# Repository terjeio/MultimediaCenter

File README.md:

# Multimedia center with DAB/FM radio

Features:

High quality (IMO) pre-amp board with I2C control of inputs and VCA based volume control.

5 line inputs, one may be fitted with an internal RIAA-preamp (phono, for moving magnet cartridges).
2 line outputs with old-style tape copy function and post listening possible.

Power amplifier on/off switching via inbuilt relay river.

KeyStone DAB/FM-module may be fitted.

Custom Raspberry PI power switch with PC-style startup/shutdown, may be controlled over I2C or from a front panel button.
Has "breakout" socket for internal USB HDD.

IR Remote Control - RC5 protocol: for input selection, volume control and UI controller navigation.

Main controller built around a Texas Instruments Tiva C MPU, custom UI library with support for KeyStone radio-module.

Raspberry PI for media playback (via Kodi), in my configuration audio is fed via HDMI to a TV and then to a DAC mounted inside the pre-amp cabinet.

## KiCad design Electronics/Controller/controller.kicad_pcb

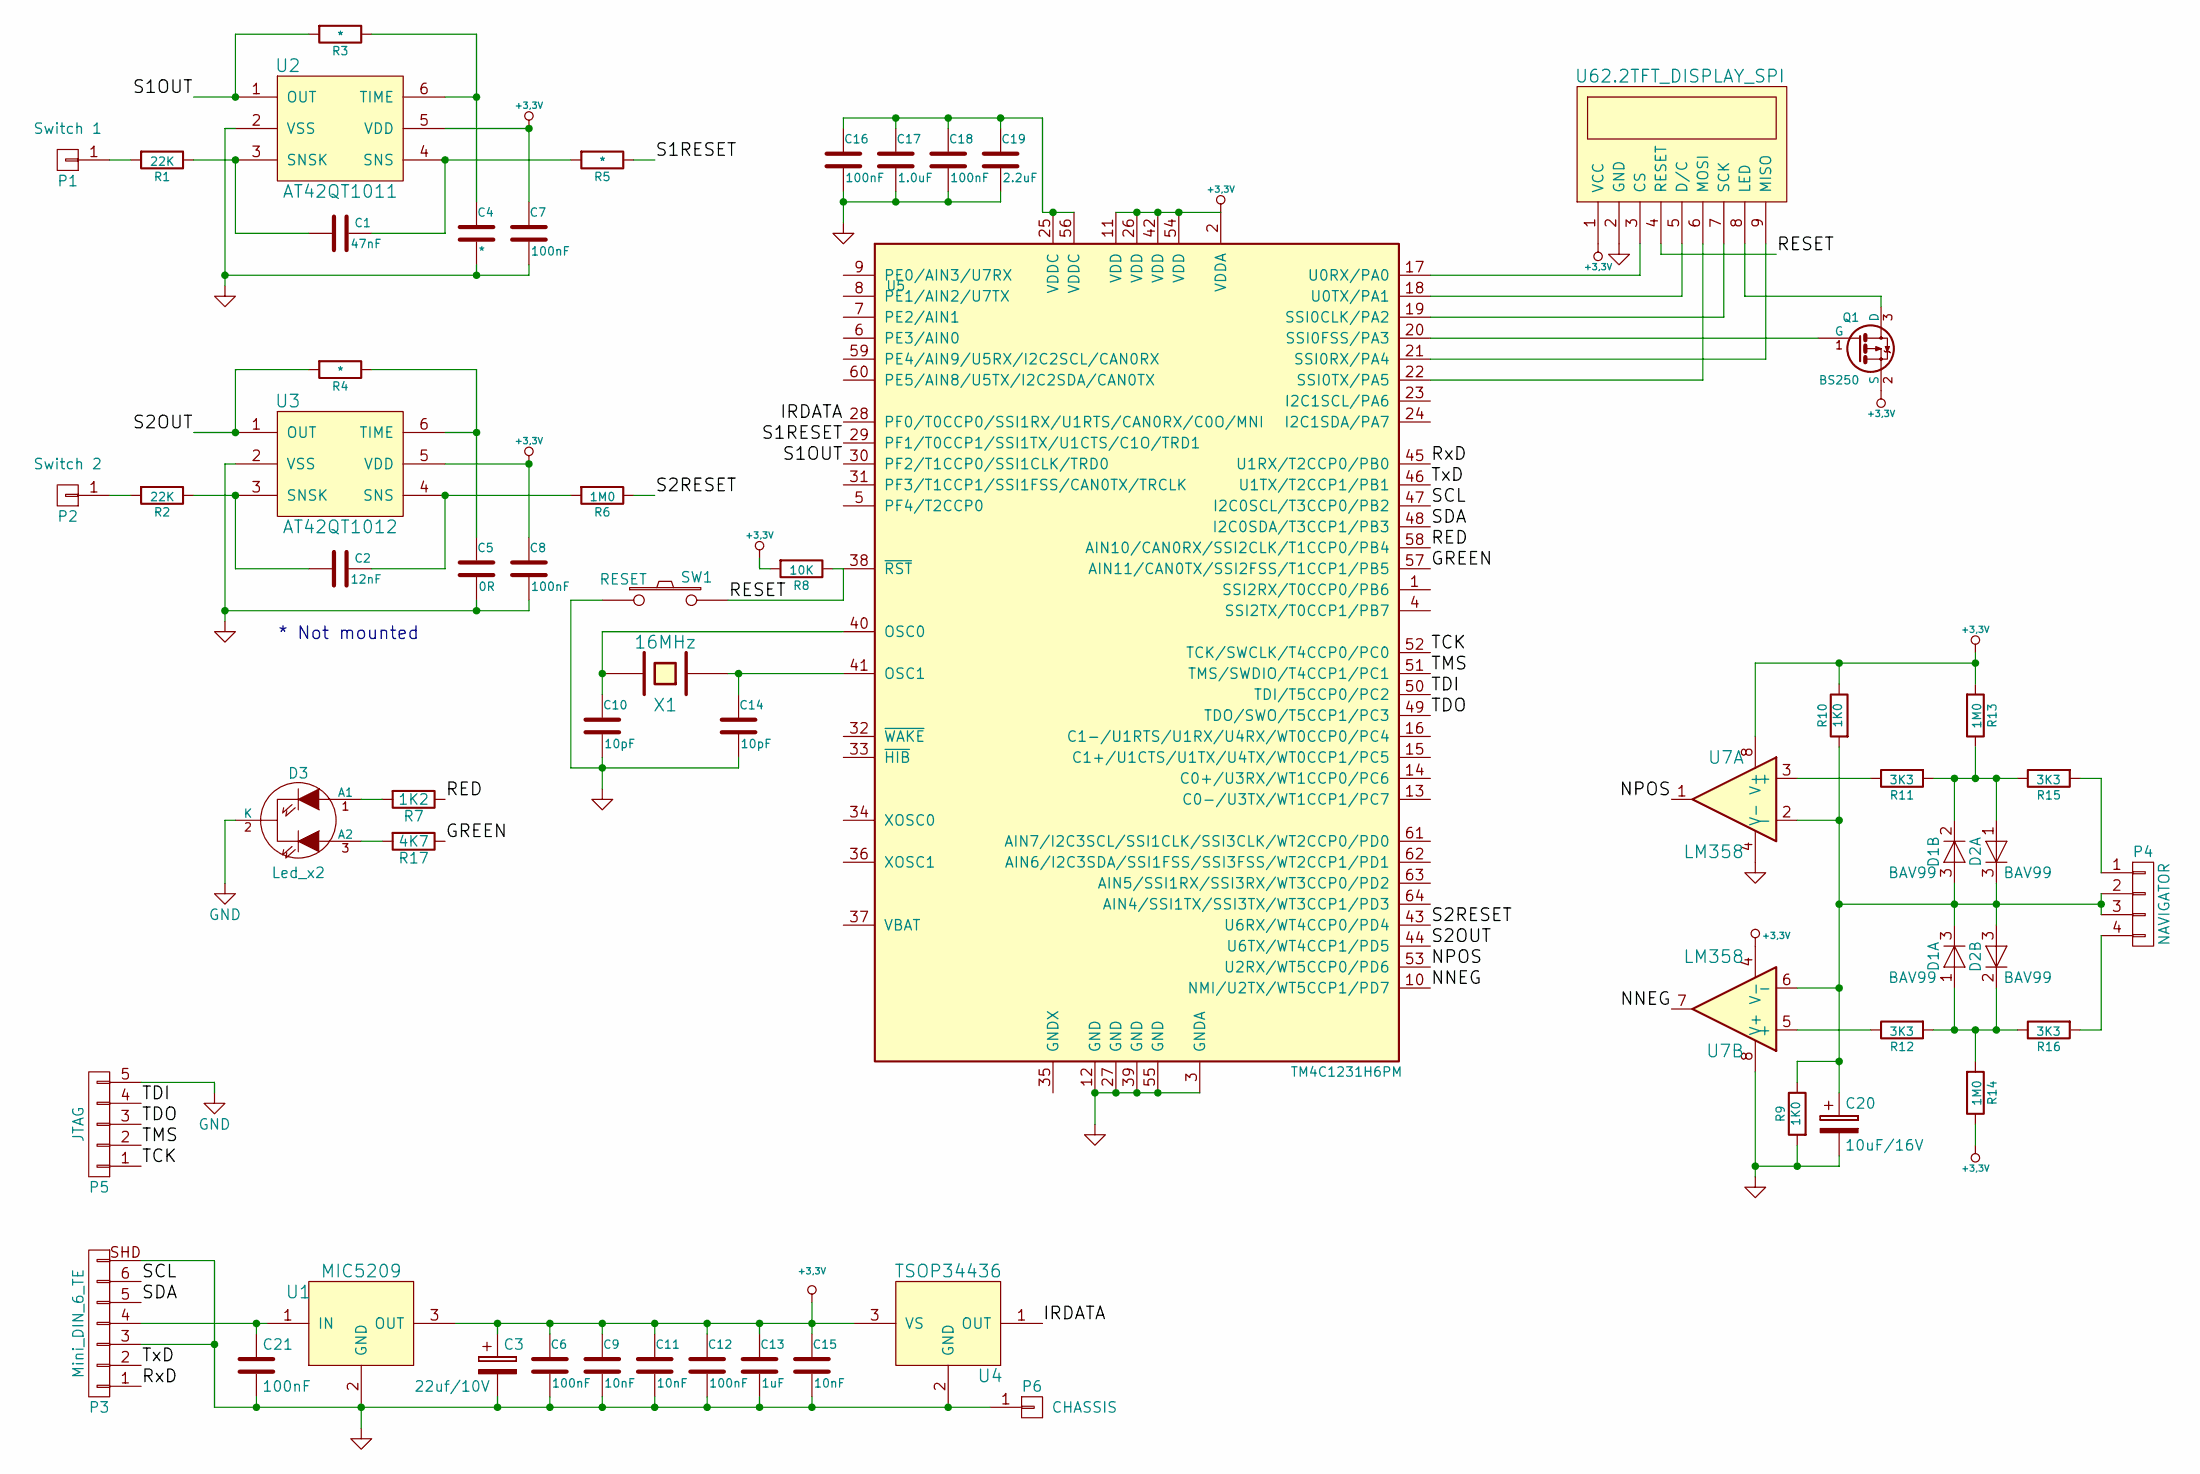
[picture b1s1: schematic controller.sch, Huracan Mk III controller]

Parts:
C1: 47nF; C_0805
C2: 12nF; C_0805
C3: 22uf/10V; TantalC_SizeA_EIA-3216_Reflow
C4: *; C_0805
C5: 0R; C_0805
C6, C7, C8, C12, C16, C18, C21: 100nF; C_0805
C9, C11, C15: 10nF; C_0805
C10, C14: 10pF; C_0805
C13: 1uF; C_0805
C17: 1.0uF; C_0805
C19: 2.2uF; C_1206
C20: 10uF/16V; TantalC_SizeA_EIA-3216_Reflow
D1, D2: BAV99; SOT-23
D3: Led_x2; LED-3MM-2
P1: Switch 1; Pin_Header_Straight_1x01
P2: Switch 2; Pin_Header_Straight_1x01
P3: Mini_DIN_6_TE; Mini_DIN_6_TE_Connectivity
P4: NAVIGATOR; Pin_Header_Straight_1x04
P5: JTAG; Pin_Header_Straight_1x05
P6: CHASSIS; Socket_Strip_Straight_1x01
Q1: BS250; SOT-23
R1, R2: 22K; R_1206
R3, R4, R5: *; R_1206
R6, R13, R14: 1M0; R_1206
R7: 1K2; R_1206
R8: 10K; R_1206
R9, R10: 1K0; R_1206
R11, R12, R15, R16: 3K3; R_1206
R17: 4K7; R_1206
SW1: RESET; SWITCH_TAC_H7.3
U1: MIC5209; SOT223
U2: AT42QT1011; SOT23-6
U3: AT42QT1012; SOT23-6
U4: TSOP34436; Pin_Header_Straight_1x03
U5: TM4C1231H6PM; LQFP-64_10x10mm_Pitch0.5mm
U6: 2.2TFT_DISPLAY_SPI; QVGA_2.2
U7: LM358; SO-8
X1: 16MHz; XTAL_ABM7_6x3.5MM

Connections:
/GREEN: R17.1, U5.57 (AIN11/CAN0TX/SSI2FSS/T1CCP1/PB5)
/IRDATA: U4.1 (OUT), U5.28 (PF0/T0CCP0/SSI1RX/U1RTS/CAN0RX/C0O/MNI)
/NNEG: U5.10 (NMI/U2TX/WT5CCP1/PD7), U7.7
/NPOS: U5.53 (U2RX/WT5CCP0/PD6), U7.1
/RED: R7.1, U5.58 (AIN10/CAN0RX/SSI2CLK/T1CCP0/PB4)
/RESET: R8.1, SW1.2, U5.38 (~RST~), U6.4 (RESET)
/RxD: P3.1, U5.45 (U1RX/T2CCP0/PB0)
/S1OUT: R3.2, U2.1 (OUT), U5.30 (PF2/T1CCP0/SSI1CLK/TRD0)
/S1RESET: R5.1, U5.29 (PF1/T0CCP1/SSI1TX/U1CTS/C1O/TRD1)
/S2OUT: R4.2, U3.1 (OUT), U5.44 (U6TX/WT4CCP1/PD5)
/S2RESET: R6.1, U5.43 (U6RX/WT4CCP0/PD4)
/SCL: P3.6, U5.47 (I2C0SCL/T3CCP0/PB2)
/SDA: P3.5, U5.48 (I2C0SDA/T3CCP1/PB3)
/TCK: P5.1, U5.52 (TCK/SWCLK/T4CCP0/PC0)
/TDI: P5.4, U5.50 (TDI/T5CCP0/PC2)
/TDO: P5.3, U5.49 (TDO/SWO/T5CCP1/PC3)
/TMS: P5.2, U5.51 (TMS/SWDIO/T4CCP1/PC1)
/TxD: P3.2, U5.46 (U1TX/T2CCP1/PB1)
unnamed: C1.1, R1.1, U2.3 (SNSK)
unnamed: C1.2, R5.2, U2.4 (SNS)
unnamed: C2.1, R2.1, U3.3 (SNSK)
unnamed: C2.2, R6.2, U3.4 (SNS)
unnamed: C4.1, R3.1, U2.6 (TIME)
unnamed: C5.1, R4.1, U3.6 (TIME)
unnamed: C10.1, U5.40 (OSC0), X1.2
unnamed: C14.1, U5.41 (OSC1), X1.1
unnamed: C16.1, C17.1, C18.1, C19.1, U5.25 (VDDC), U5.56 (VDDC)
unnamed: C20.1, D1.3 (K), D2.3 (K), P4.2, P4.3, R9.1, R10.2, U7.2 (-), U7.6 (-)
unnamed: C21.1, P3.4, U1.1 (IN)
unnamed: D1.1 (A), D2.2 (K), R12.2, R14.2, R16.1
unnamed: D1.2 (K), D2.1 (A), R11.2, R13.1, R15.1
unnamed: D3.1 (A1), R7.2
unnamed: D3.3 (A2), R17.2
unnamed: P1.1, R1.2
unnamed: P2.1, R2.2
unnamed: P4.1, R15.2
unnamed: P4.4, R16.2
unnamed: Q1.1 (G), U5.20 (SSI0FSS/PA3)
unnamed: Q1.3 (D), U6.8 (LED)
unnamed: R11.1, U7.3 (+)
unnamed: R12.1, U7.5 (+)
unnamed: U5.17 (U0RX/PA0), U6.3 (CS)
unnamed: U5.18 (U0TX/PA1), U6.5 (D/C)
unnamed: U5.19 (SSI0CLK/PA2), U6.7 (SCK)
unnamed: U5.21 (SSI0RX/PA4), U6.9 (MISO)
unnamed: U5.22 (SSI0TX/PA5), U6.6 (MOSI)

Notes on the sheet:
* Not mounted

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
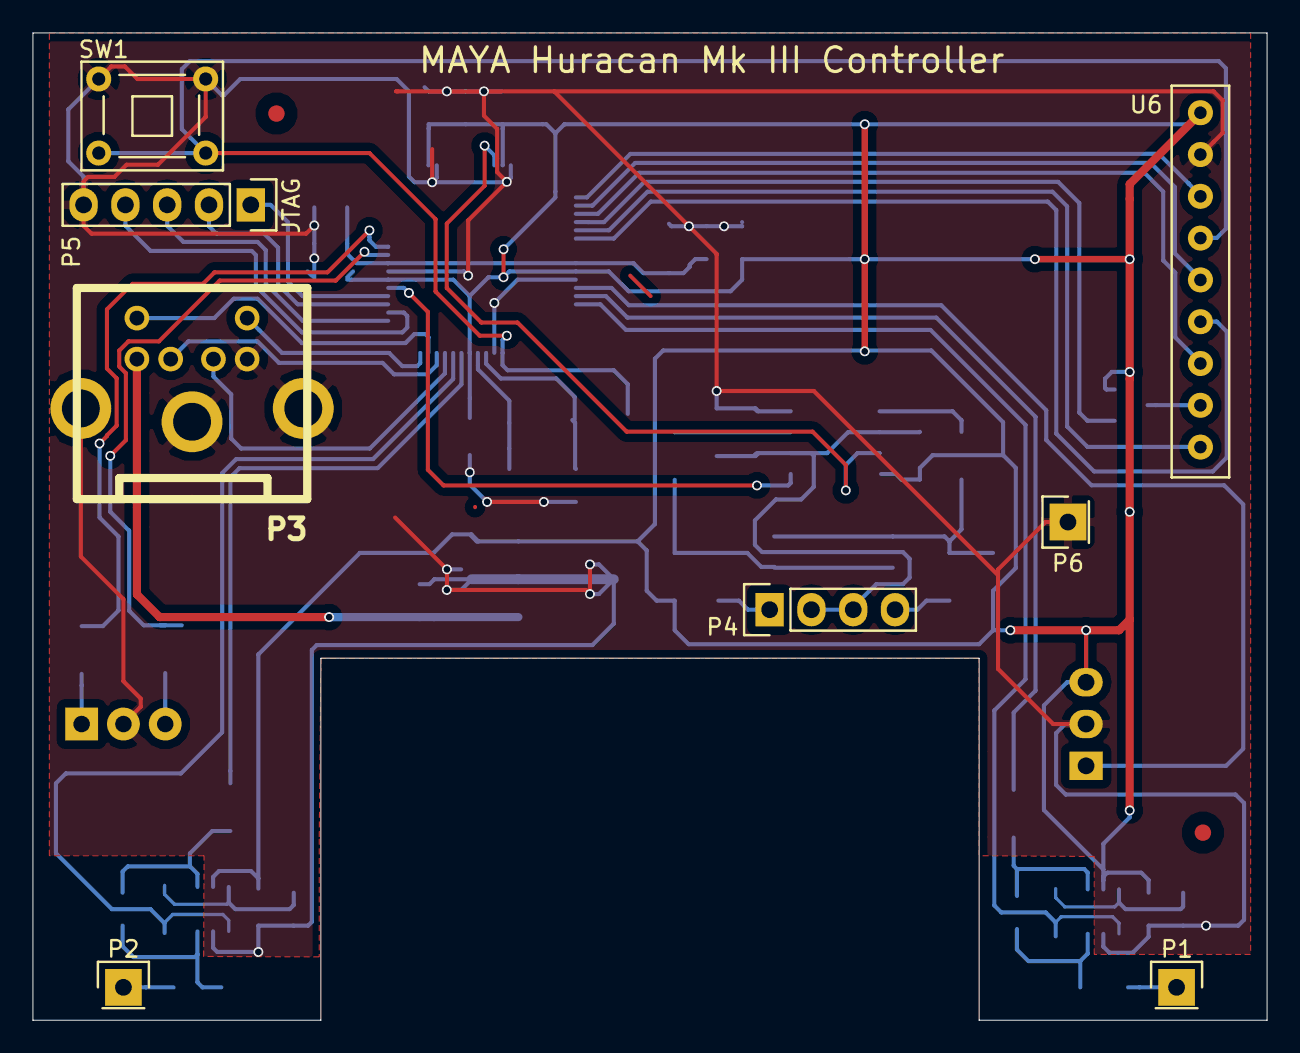
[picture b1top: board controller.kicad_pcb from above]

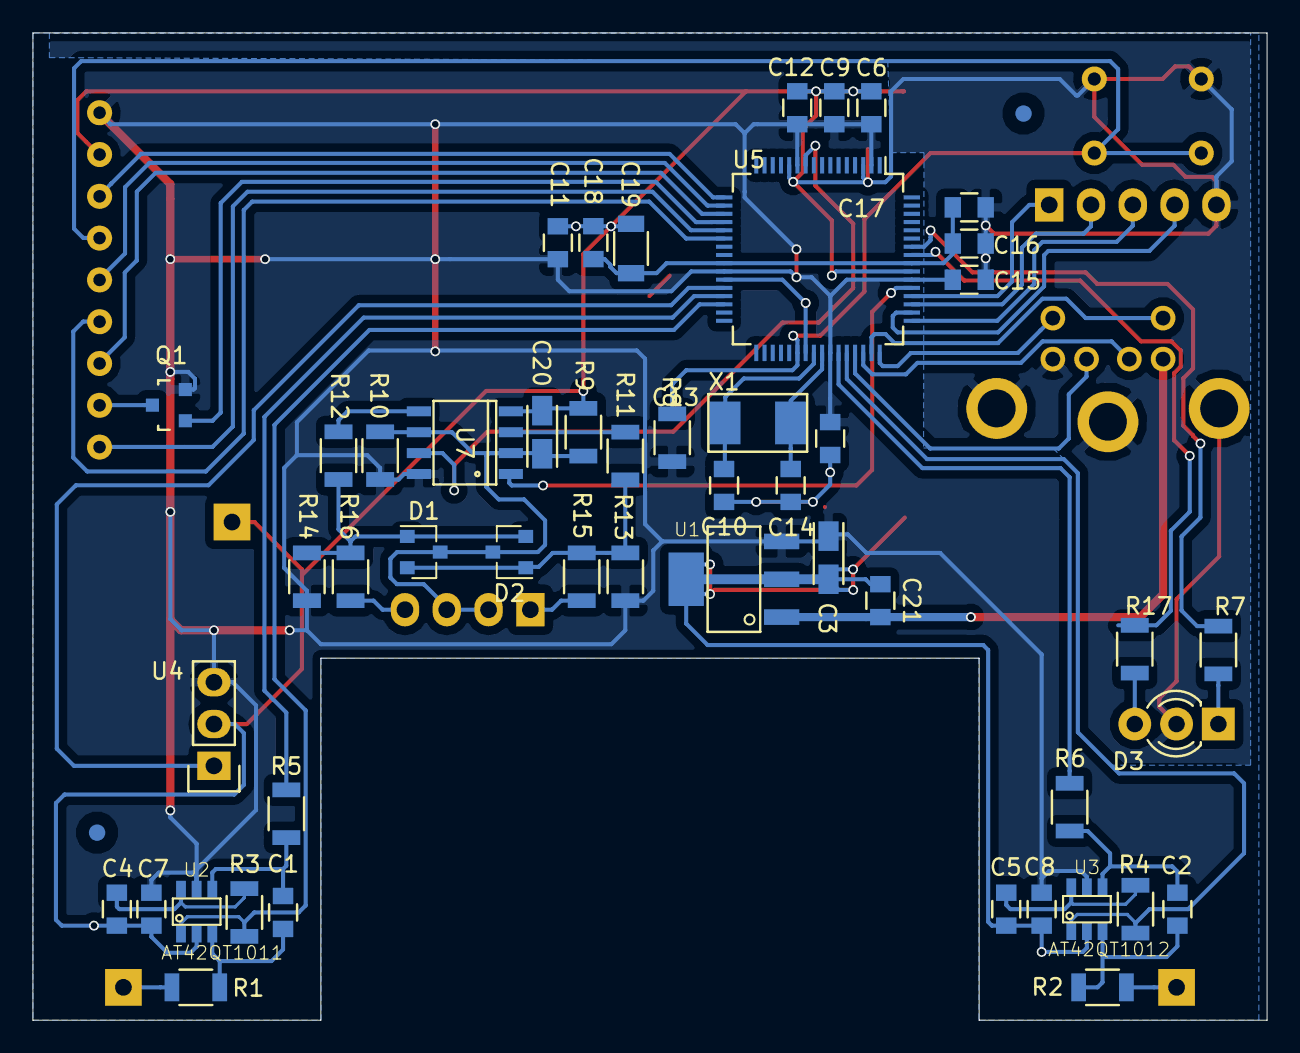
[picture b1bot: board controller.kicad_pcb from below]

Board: 2 copper layers, 75.0 x 60.0 mm, 57 parts (49 on the bottom side), 48 nets.

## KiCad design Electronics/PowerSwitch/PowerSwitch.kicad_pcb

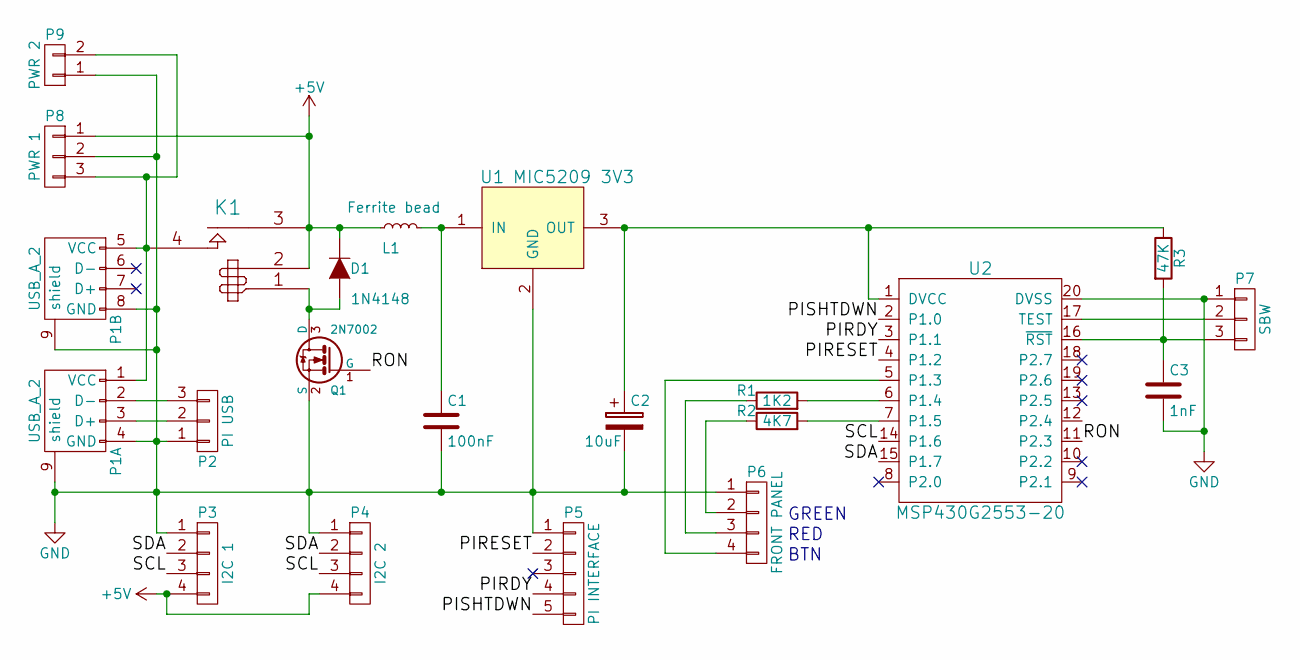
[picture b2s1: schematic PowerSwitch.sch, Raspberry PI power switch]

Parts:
C1: 100nF; C_1206
C2: 10uF; TantalC_SizeA_EIA-3216_Reflow
C3: 1nF; C_1206
D1: 1N4148; SOD-123
K1: RELAY-LD-P; PANASONIC_LD_P_RELAY
L1: Ferrite bead; Resistor_Horizontal_RM10mm
P1: USB_A_2
P2: PI USB; Pin_Header_Straight_1x03
P3: I2C 1; Pin_Header_Straight_1x04
P4: I2C 2; Pin_Header_Straight_1x04
P5: PI INTERFACE; Pin_Header_Straight_1x05
P6: FRONT PANEL; Pin_Header_Straight_1x04
P7: SBW; Pin_Header_Straight_1x03
P8: PWR 1; CONN_PWR_3P
P9: PWR 2; Pin_Header_Straight_1x02
Q1: 2N7002; SOT-23
R1: 1K2; R_1206
R2: 4K7; R_1206
R3: 47K; R_1206
U1: MIC5209 3V3; AB2_SOT223
U2: MSP430G2553-20; TSSOP20

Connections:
+5V: D1.1 (K), K1.2, K1.3, L1.1, P3.4, P4.4, P8.1
/PIRDY: P5.4, U2.3 (P1.1)
/PIRESET: P5.2, U2.4 (P1.2)
/PISHTDWN: P5.5, U2.2 (P1.0)
/RON: Q1.1 (G), U2.11 (P2.3)
/SCL: P3.3, P4.3, U2.14 (P1.6)
/SDA: P3.2, P4.2, U2.15 (P1.7)
GND: C1.2, C2.2, C3.2, P1.4 (GND), P1.8 (GND), P1.9 (shield), P2.1, P3.1, P4.1, P5.1, P6.1, P7.1, P8.2, P9.1, Q1.2 (S), U1.2 (GND), U2.20 (DVSS)
unnamed: C1.1, L1.2, U1.1 (IN)
unnamed: C2.1, R3.1, U1.3 (OUT), U2.1 (DVCC)
unnamed: C3.1, P7.3, R3.2, U2.16 (~RST~)
unnamed: D1.2 (A), K1.1, Q1.3 (D)
unnamed: K1.4, P1.1 (VCC), P1.5 (VCC), P8.3, P9.2
unnamed: P1.2 (D-), P2.3
unnamed: P1.3 (D+), P2.2
unnamed: P6.2, R2.1
unnamed: P6.3, R1.1
unnamed: P6.4, U2.5 (P1.3)
unnamed: P7.2, U2.17 (TEST)
unnamed: R1.2, U2.6 (P1.4)
unnamed: R2.2, U2.7 (P1.5)

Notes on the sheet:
RED
GREEN
BTN

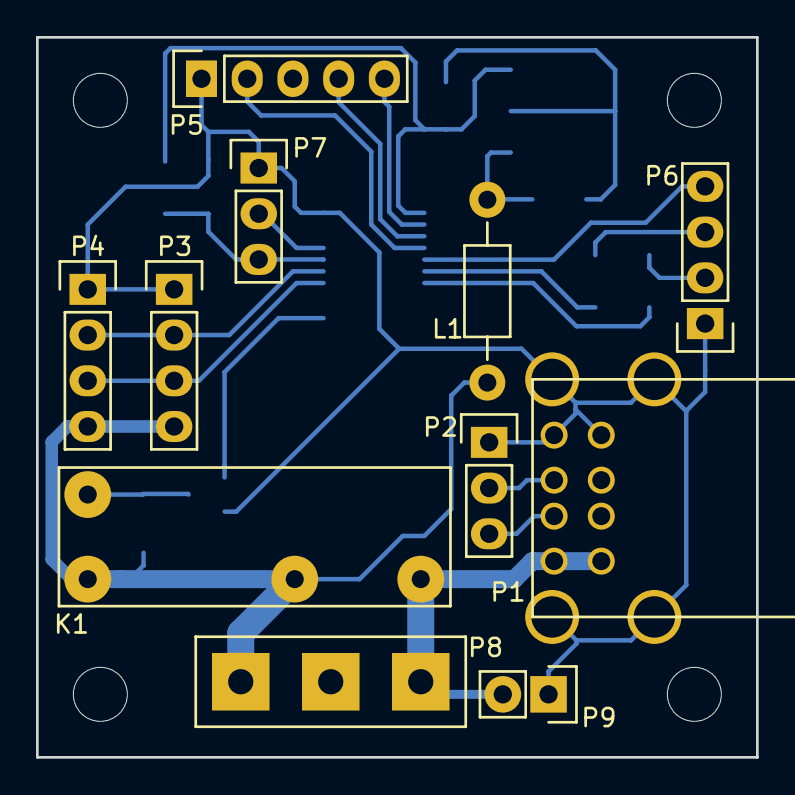
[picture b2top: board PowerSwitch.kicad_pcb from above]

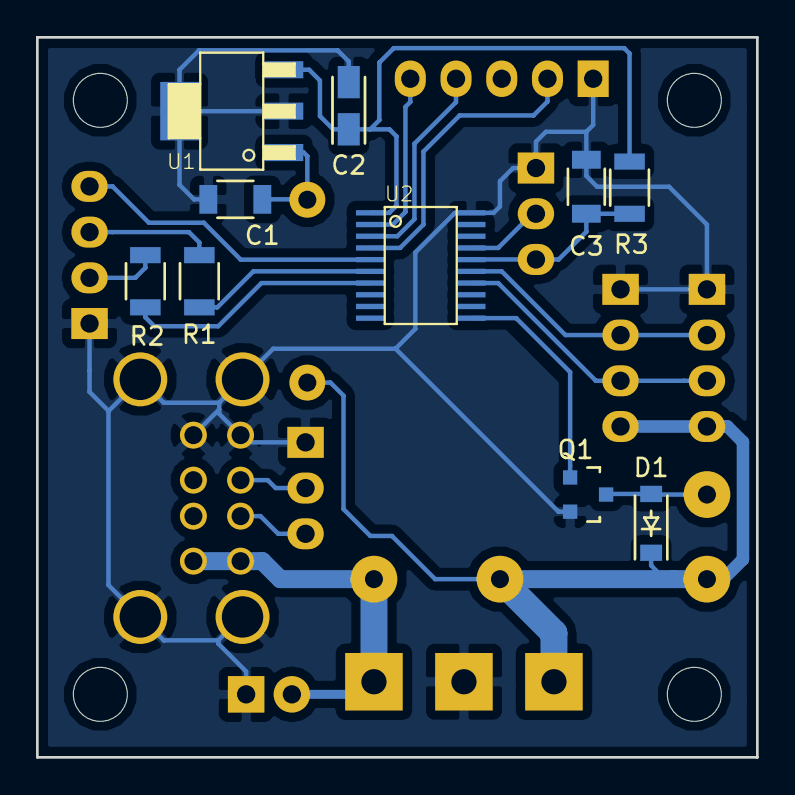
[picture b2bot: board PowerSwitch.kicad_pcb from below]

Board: 2 copper layers, 40.0 x 40.0 mm, 21 parts (10 on the bottom side), 21 nets.

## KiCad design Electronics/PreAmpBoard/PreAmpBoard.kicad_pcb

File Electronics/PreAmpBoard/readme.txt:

MAYA Huracan PreAmp MK III Rev. A by

Terje Io
Io Engineering

Licensed under CERN OHL v.1.2 or later except the RIAA-circuitry which I believe is public domain.

The RIAA-circuitry was published by now defunct danish magazine High Fidelity way back in the 1980's.
I no longer have a copy of the issue(s) related to the design so I am not sure about any related copyright
but it surely is available for non-commercial use.

NOTE: Rev A has not yet been been verified as a working design.

Firmware will be released as a separate package under a different license after the design is verified.

A limited number of PCBs might or might not be made available for purchase at cost.

Files are in KiCad format.

2017-09-18

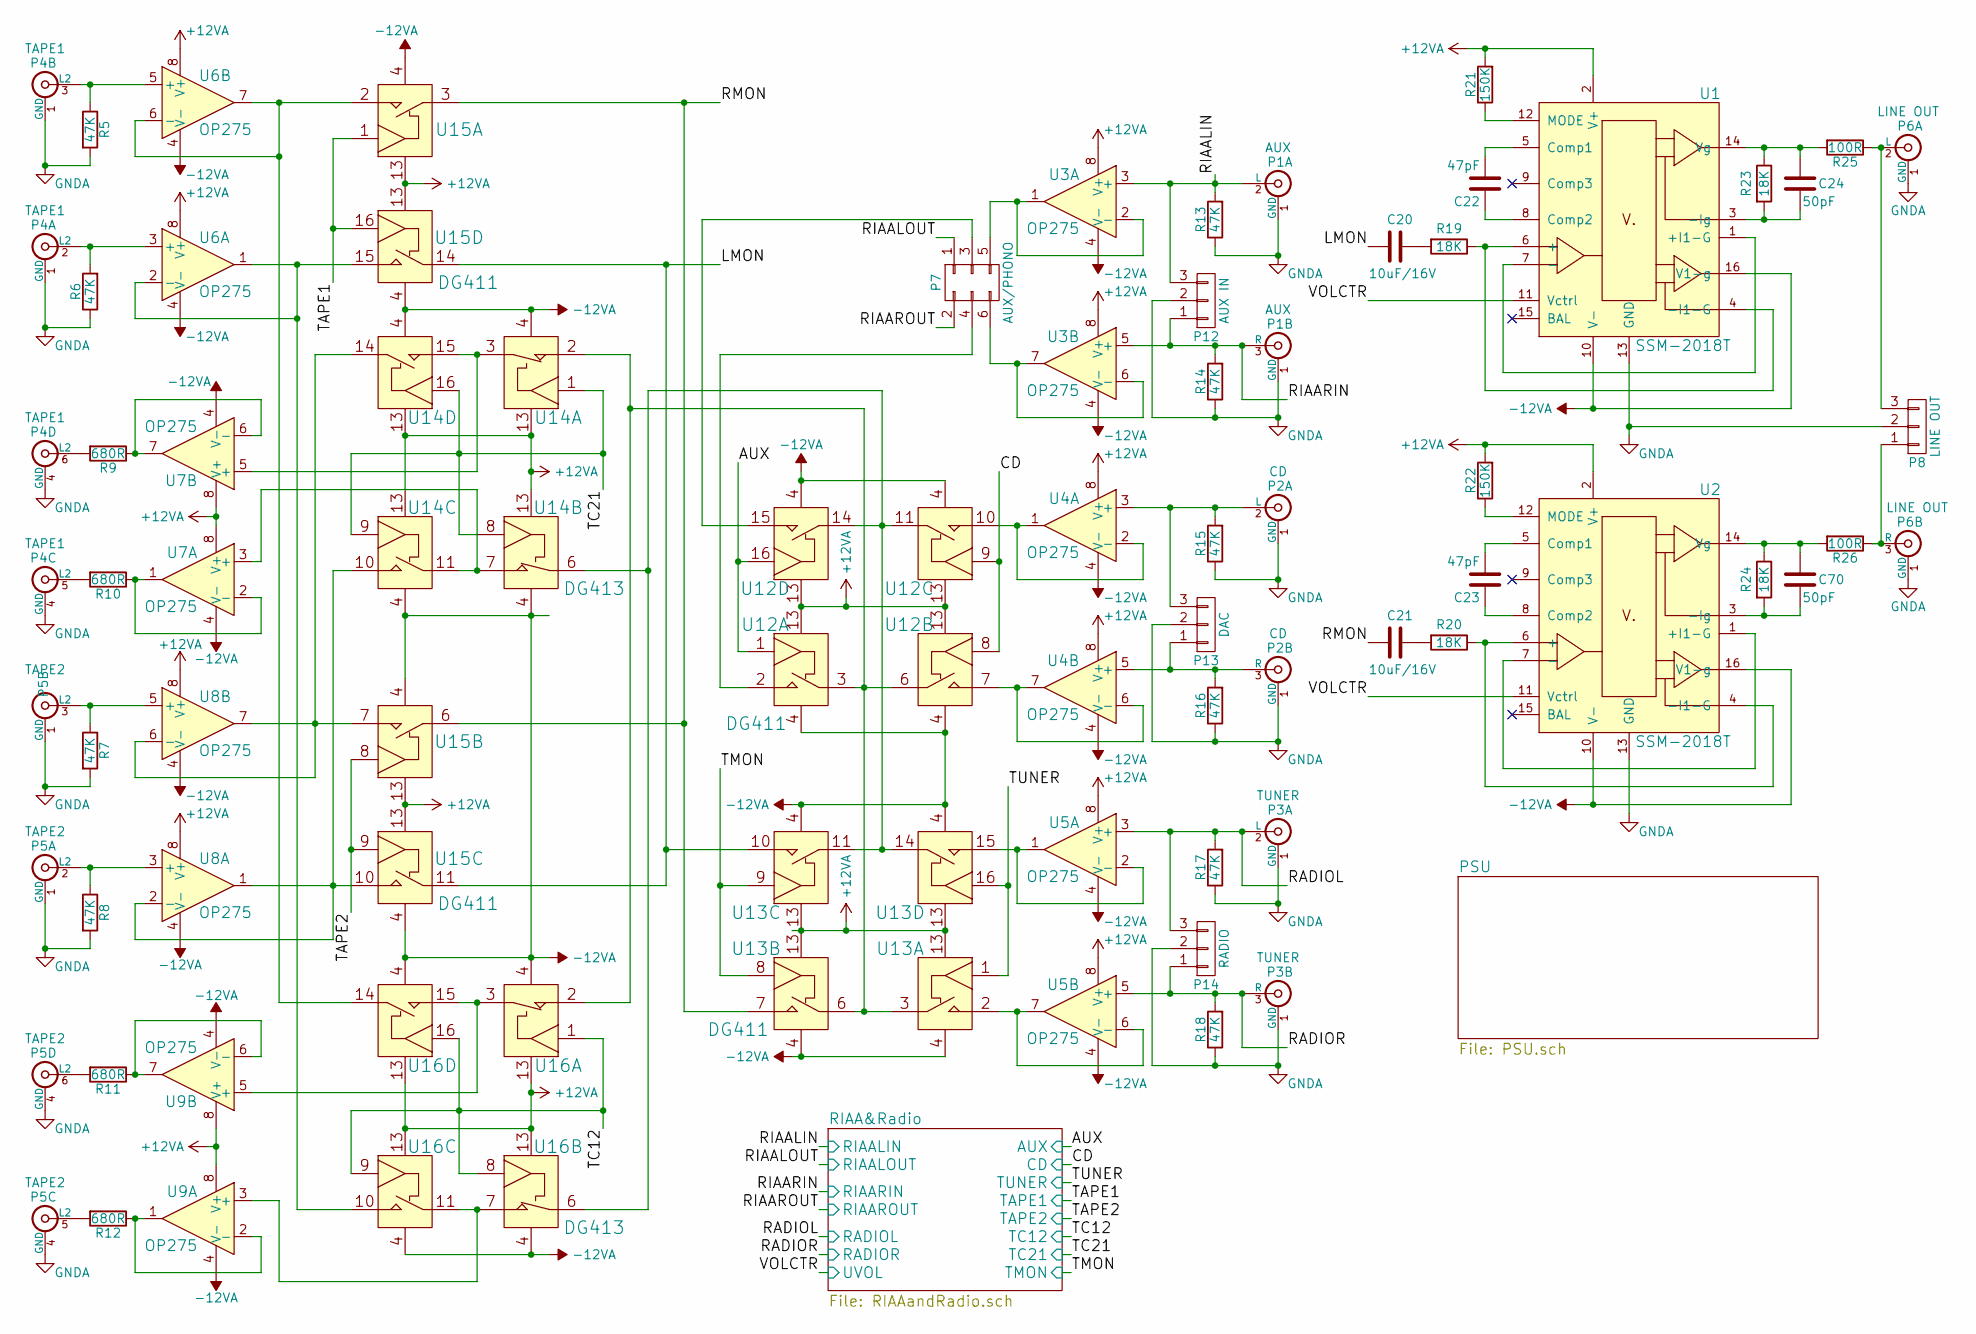
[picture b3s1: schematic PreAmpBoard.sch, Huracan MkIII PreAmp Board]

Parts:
C20, C21: 10uF/16V; C_Radial_D5_L11_P2.5
C22, C23: 47pF; C_Disc_D3_P5
C24, C70: 50pF; C_Disc_D3_P5
P1: AUX; PSG01550
P2: CD; PSG01550
P3: TUNER; PSG01550
P4: TAPE1; PSG01551
P5: TAPE2; PSG01551
P6: LINE OUT; PSG01550
P7: AUX/PHONO; Pin_Header_Straight_2x03
P8: LINE OUT; 70543-03
P12: AUX IN; 70543-03
P13: DAC; 70543-03
P14: RADIO; 70543-03
R5, R6, R7, R8, R13, R14, R15, R16, R17, R18: 47K; Resistor_Horizontal_RM10mm
R9, R10, R11, R12: 680R; Resistor_Horizontal_RM10mm
R19, R20, R23, R24: 18K; Resistor_Horizontal_RM10mm
R21, R22: 150K; Resistor_Horizontal_RM10mm
R25, R26: 100R; Resistor_Horizontal_RM10mm
U1, U2: SSM-2018T; SOIC-16_7.5x10.3mm_Pitch1.27mm
U3, U4, U5, U6, U7, U8, U9: OP275; DIP-8__300
U12, U13, U15: DG411; SOIC-16_3.9x9.9mm_Pitch1.27mm
U14, U16: DG413; SOIC-16_3.9x9.9mm_Pitch1.27mm

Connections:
+12VA: R21.2, R22.2, U1.2 (V+), U2.2 (V+), U3.8 (V+), U4.8 (V+), U5.8 (V+), U6.8 (V+), U7.8 (V+), U8.8 (V+), U9.8 (V+), U12.13 (V+), U13.13 (V+), U14.13 (V+), U15.13 (V+), U16.13 (V+); also elsewhere on the board
/AUX: U12.1 (SW), U12.16 (SW); also elsewhere on the board
/CD: U12.8 (SW), U12.9 (SW); also elsewhere on the board
/LMON: C20.2, U13.10 (IN), U15.11 (OUT), U15.14 (OUT)
/RADIOL: P3.2 (L), P14.3, R17.2, U5.3 (+); also elsewhere on the board
/RADIOR: P3.3 (R), P14.1, R18.2, U5.5 (+); also elsewhere on the board
/RIAALIN: P1.2 (L), P12.3, R13.2, U3.3 (+); also elsewhere on the board
/RIAALOUT: P7.1; also elsewhere on the board
/RIAARIN: P1.3 (R), P12.1, R14.2, U3.5 (+); also elsewhere on the board
/RIAAROUT: P7.2; also elsewhere on the board
/RMON: C21.2, U13.7 (IN), U15.3 (OUT), U15.6 (OUT)
/TAPE1: U15.1 (SW), U15.16 (SW); also elsewhere on the board
/TAPE2: U15.8 (SW), U15.9 (SW); also elsewhere on the board
/TC12: U16.1 (SW), U16.8 (SW), U16.9 (SW), U16.16 (SW); also elsewhere on the board
/TC21: U14.1 (SW), U14.8 (SW), U14.9 (SW), U14.16 (SW); also elsewhere on the board
/TMON: U13.8 (SW), U13.9 (SW); also elsewhere on the board
/TUNER: U13.1 (SW), U13.16 (SW); also elsewhere on the board
/VOLCTR: U1.11 (Vctrl), U2.11 (Vctrl); also elsewhere on the board
GND: P1.1 (GND), P2.1 (GND), P3.1 (GND), P4.1 (GND), P4.4 (GND), P5.1 (GND), P5.4 (GND), P6.1 (GND), P8.2, P12.2, P13.2, P14.2, R5.2, R6.1, R7.2, R8.2, R13.1, R14.1, R15.1, R16.1, R17.1, R18.1, U1.13 (GND), U2.13 (GND), U12.5 (GND), U13.5 (GND), U14.5 (GND), U15.5 (GND), U16.5 (GND); also elsewhere on the board
unnamed: C20.1, R19.2
unnamed: C21.1, R20.2
unnamed: C22.1, U1.8 (Comp2)
unnamed: C22.2, U1.5 (Comp1)
unnamed: C23.1, U2.8 (Comp2)
unnamed: C23.2, U2.5 (Comp1)
unnamed: C24.1, R23.2, U1.3 (-Ig)
unnamed: C24.2, R23.1, R25.2, U1.14 (Vg)
unnamed: C70.1, R24.2, U2.3 (-Ig)
unnamed: C70.2, R24.1, R26.2, U2.14 (Vg)
unnamed: P4.2 (L2), R6.2, U6.3 (+)
unnamed: P4.3 (L2), R5.1, U6.5 (+)
unnamed: P4.5 (L2), R10.2
unnamed: P4.6 (L2), R9.2
unnamed: P5.2 (L2), R8.1, U8.3 (+)
unnamed: P5.3 (L2), R7.1, U8.5 (+)
unnamed: P5.5 (L2), R12.2
unnamed: P5.6 (L2), R11.2
unnamed: P6.2 (L), P8.3, R25.1
unnamed: P6.3 (R), P8.1, R26.1
unnamed: P7.3, U12.15 (IN)
unnamed: P7.4, U12.2 (IN)
unnamed: P2.3 (R), P13.1, R16.2, U4.5 (+)
unnamed: P2.2 (L), P13.3, R15.2, U4.3 (+)
unnamed: R19.1, U1.4 (-I1-G), U1.6 (+)
unnamed: R20.1, U2.4 (-I1-G), U2.6 (+)
unnamed: R21.1, U1.12 (MODE)
unnamed: R22.1, U2.12 (MODE)
unnamed: U1.1 (+I1-G), U1.7 (-)
unnamed: U2.1 (+I1-G), U2.7 (-)
unnamed: U12.3 (OUT), U12.6 (OUT), U13.3 (OUT), U13.6 (OUT), U14.2 (IN), U16.2 (IN)
unnamed: U12.11 (OUT), U12.14 (OUT), U13.11 (OUT), U13.14 (OUT), U14.6 (OUT), U16.6 (OUT)
unnamed: U7.3 (+), U14.7 (IN), U14.11 (OUT)
unnamed: U7.5 (+), U14.3 (OUT), U14.15 (IN)
unnamed: U9.3 (+), U16.7 (IN), U16.11 (OUT)
unnamed: U9.5 (+), U16.3 (OUT), U16.15 (IN)
VCC: U12.12 (VCC), U13.12 (VCC), U14.12 (VCC), U15.12 (VCC), U16.12 (VCC); also elsewhere on the board

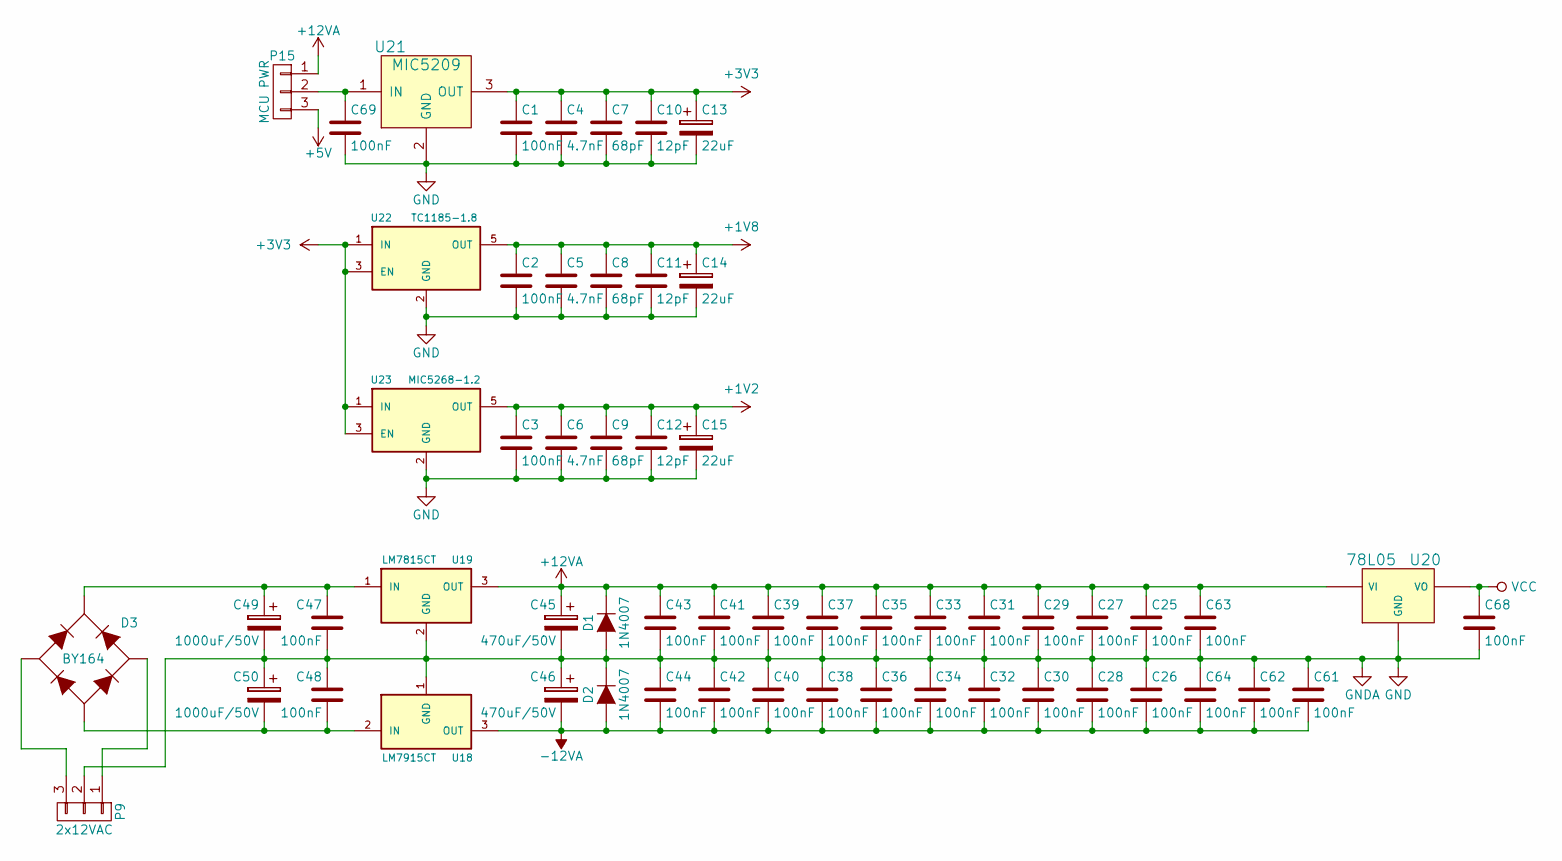
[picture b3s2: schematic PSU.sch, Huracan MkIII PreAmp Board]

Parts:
C1, C2, C3, C68, C69: 100nF; C_1206
C4, C5, C6: 4.7nF; C_0805
C7, C8, C9: 68pF; C_0805
C10, C11, C12: 12pF; C_0805
C13, C14, C15: 22uF; TantalC_SizeA_EIA-3216_Reflow
C25, C26, C27, C28, C29, C30, C31, C32, C33, C34, C35, C36, C37, C38, C39, C40, C41, C42, C43, C44, C47, C48, C61, C62, C63, C64: 100nF; C_Disc_D3_P5
C45, C46: 470uF/50V; C_Radial_D10_L20_P5
C49, C50: 1000uF/50V; C_Radial_D16_L25_P7.5
D1, D2: 1N4007; Diode_DO-41_SOD81_Horizontal_RM10
D3: BY164; BRIDGE_RECTIFIER_5MM
P9: 2x12VAC; CONN_PWR_3P
P15: MCU PWR; Pin_Header_Straight_1x03
U18: LM7915CT; TO-220-10x15VFIN
U19: LM7815CT; TO-220-10x15VFIN
U20: 78L05; TO-92_Inline_Narrow_Oval
U21: MIC5209; SOT223
U22: TC1185-1.8; SOT-23-5
U23: MIC5268-1.2; SOT-23-5

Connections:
+1V2: C3.1, C6.1, C9.1, C12.1, C15.1, U23.5 (OUT); also elsewhere on the board
+1V8: C2.1, C5.1, C8.1, C11.1, C14.1, U22.5 (OUT); also elsewhere on the board
+3V3: C1.1, C4.1, C7.1, C10.1, C13.1, U21.3 (OUT), U22.1 (IN), U22.3 (EN), U23.1 (IN), U23.3 (EN); also elsewhere on the board
+5V: P15.3
+12VA: C25.1, C27.1, C29.1, C31.1, C33.1, C35.1, C37.1, C39.1, C41.1, C43.1, C45.1, C63.1, D1.1 (K), P15.1, U19.3 (OUT), U20.3 (VI); also elsewhere on the board
GND: C1.2, C2.2, C3.2, C4.2, C5.2, C6.2, C7.2, C8.2, C9.2, C10.2, C11.2, C12.2, C13.2, C14.2, C15.2, C25.2, C26.1, C27.2, C28.1, C29.2, C30.1, C31.2, C32.1, C33.2, C34.1, C35.2, C36.1, C37.2, C38.1, C39.2, C40.1, C41.2, C42.1, C43.2, C44.1, C45.2, C46.1, C47.2, C48.1, C49.2, C50.1, C61.1, C62.1, C63.2, C64.1, C68.2, C69.2, D1.2 (A), D2.1 (K), P9.2, U18.1 (GND), U19.2 (GND), U20.2 (GND), U21.2 (GND), U22.2 (GND), U23.2 (GND); also elsewhere on the board
unnamed: C47.1, C49.1, D3.4 (+), U19.1 (IN)
unnamed: C48.2, C50.2, D3.1 (-), U18.2 (IN)
unnamed: C69.1, P15.2, U21.1 (IN)
unnamed: D3.2 (AC), P9.3
unnamed: D3.3 (AC), P9.1
VCC: C68.1, U20.1 (VO); also elsewhere on the board
